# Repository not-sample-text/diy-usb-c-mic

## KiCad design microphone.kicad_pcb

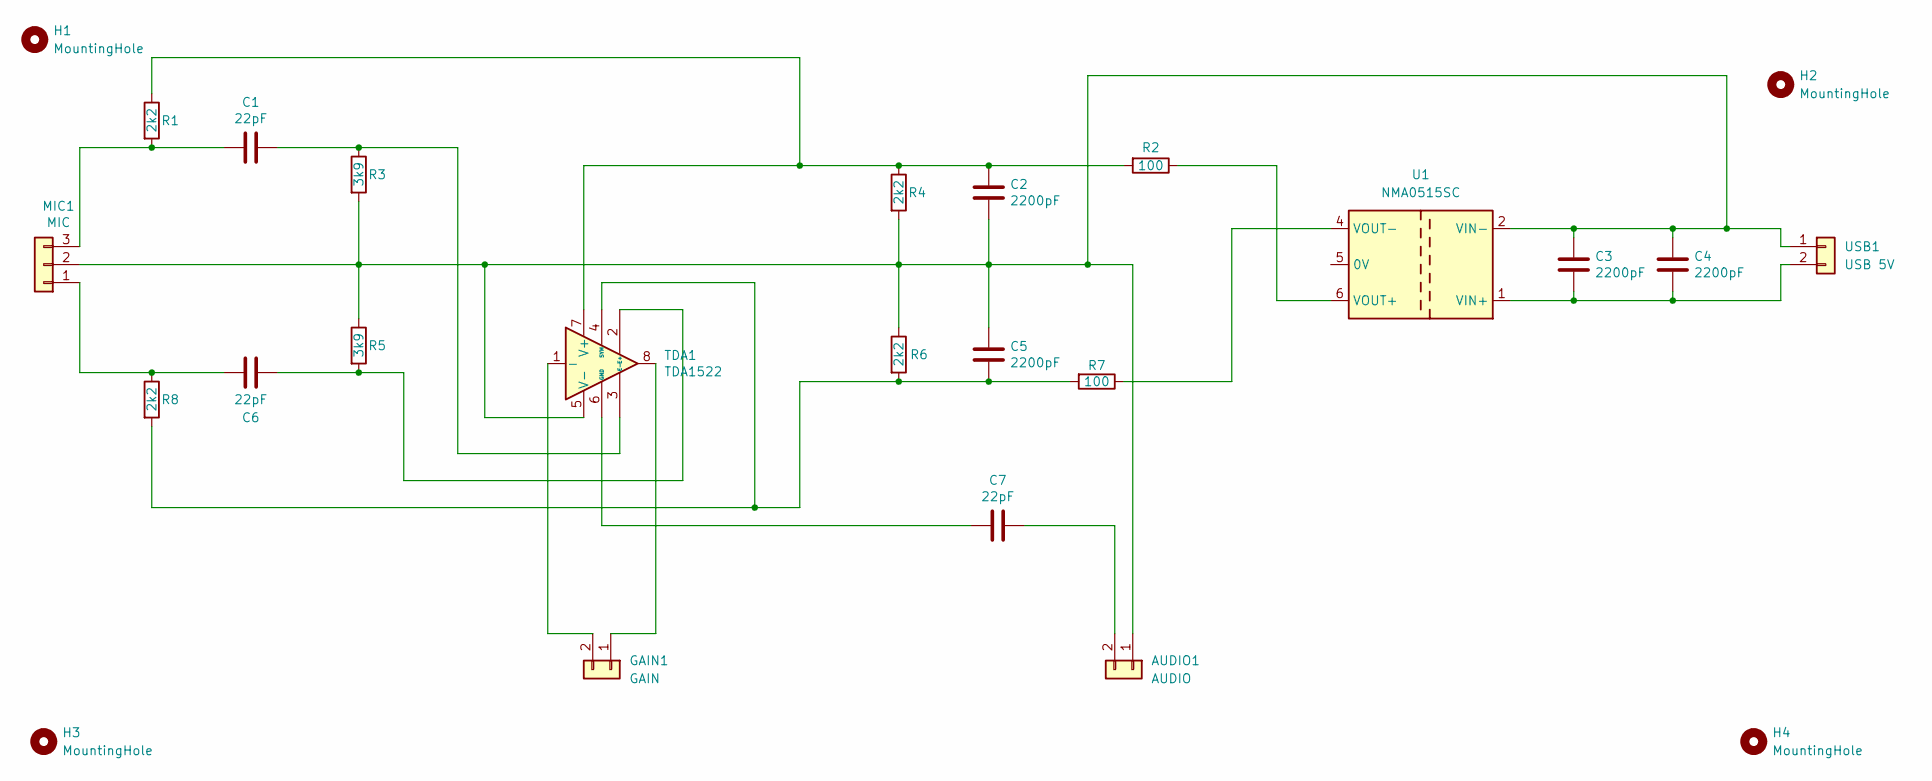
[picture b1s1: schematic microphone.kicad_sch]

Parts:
AUDIO1: AUDIO; JST_XH_B2B-XH-A_1x02_P2.50mm_Vertical
C1, C6, C7: 22pF; CP_Radial_D7.5mm_P2.50mm
C2, C3, C4, C5: 2200pF; CP_Radial_D12.5mm_P2.50mm
GAIN1: GAIN; JST_XH_B2B-XH-A_1x02_P2.50mm_Vertical
H1, H2, H3, H4: MountingHole; MountingHole_2.2mm_M2
MIC1: MIC; JST_XH_B3B-XH-A_1x03_P2.50mm_Vertical
R1, R4, R6, R8: 2k2; R_Axial_DIN0204_L3.6mm_D1.6mm_P7.62mm_Horizontal
R2, R7: 100; R_Axial_DIN0204_L3.6mm_D1.6mm_P7.62mm_Horizontal
R3, R5: 3k9; R_Axial_DIN0204_L3.6mm_D1.6mm_P7.62mm_Horizontal
TDA1: TDA1522; DIP-8_W8.89mm_SMDSocket_LongPads
U1: NMA0515SC; Converter_DCDC_Murata_NMAxxxxSC_THT
USB1: USB 5V; JST_XH_B2B-XH-A_1x02_P2.50mm_Vertical

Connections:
unnamed: AUDIO1.1, C2.1, C3.2, C4.2, C5.2, MIC1.2, R3.2, R4.2, R5.1, R6.1, TDA1.5 (V-), U1.2 (VIN-), USB1.1
unnamed: AUDIO1.2, C7.1
unnamed: GAIN1.1, TDA1.8
unnamed: GAIN1.2, TDA1.1 (-)
unnamed: C6.2, MIC1.1, R8.1
unnamed: C1.2, MIC1.3, R1.2
unnamed: C6.1, R5.2, TDA1.2 (E+)
unnamed: C1.1, R3.1, TDA1.3 (E-)
unnamed: C7.2, TDA1.6 (GND)
unnamed: C5.1, R6.2, R7.2, R8.2, TDA1.4 (SYM)
unnamed: C2.2, R1.1, R2.2, R4.1, TDA1.7 (V+)
unnamed: C3.1, C4.1, U1.1 (VIN+), USB1.2
unnamed: R2.1, U1.6 (VOUT+)
unnamed: R7.1, U1.4 (VOUT-)

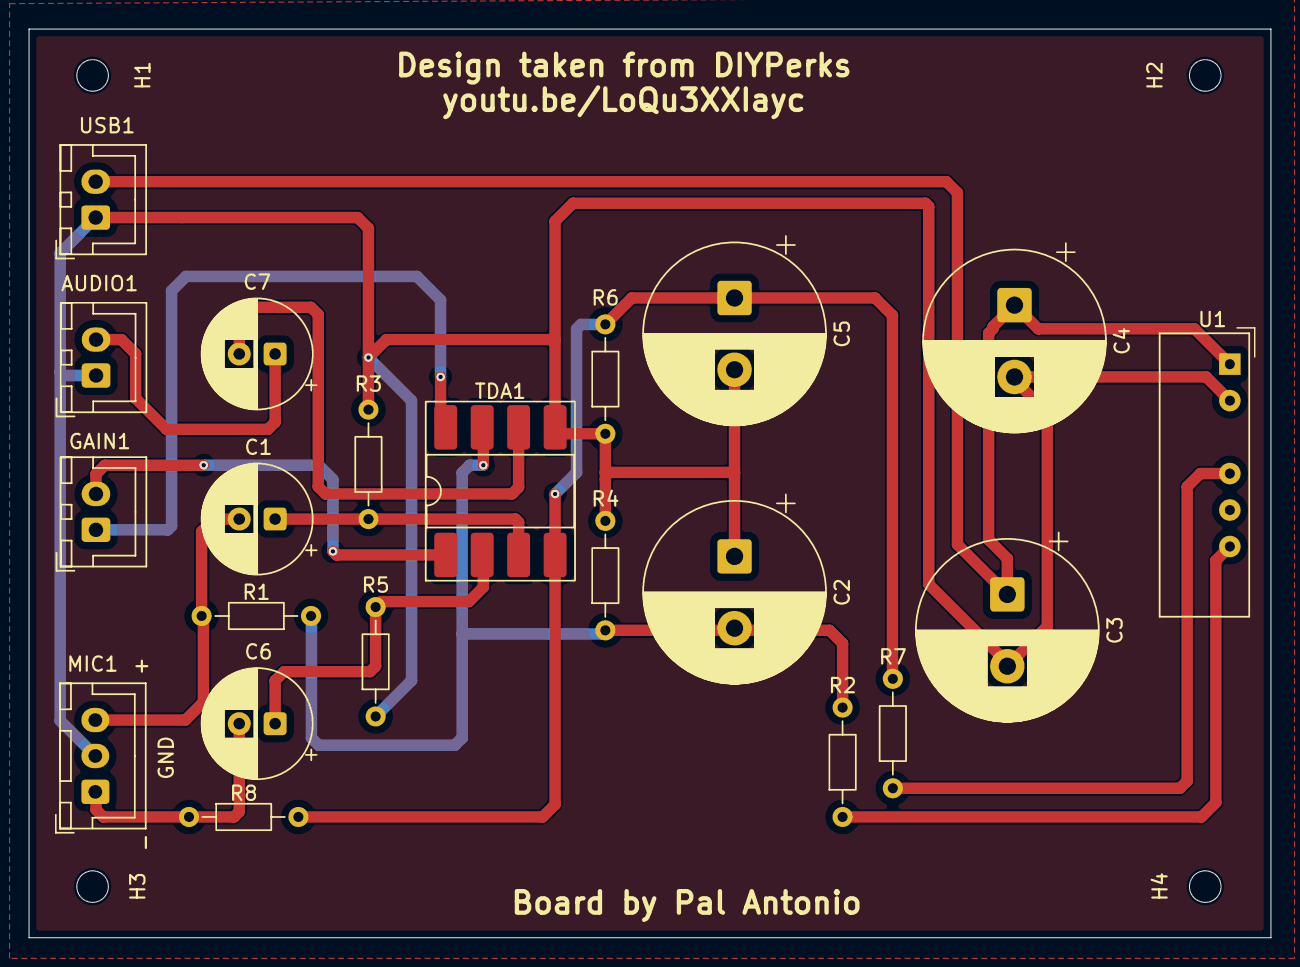
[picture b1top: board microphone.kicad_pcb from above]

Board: 2 copper layers, 86.5 x 63.3 mm, 25 parts (0 on the bottom side), 14 nets.

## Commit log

2025-05-20 Add Mounting Hole symbols and update references in schematic - Created a new design rule file (DRU) with custom DRC settings for PCBWay
